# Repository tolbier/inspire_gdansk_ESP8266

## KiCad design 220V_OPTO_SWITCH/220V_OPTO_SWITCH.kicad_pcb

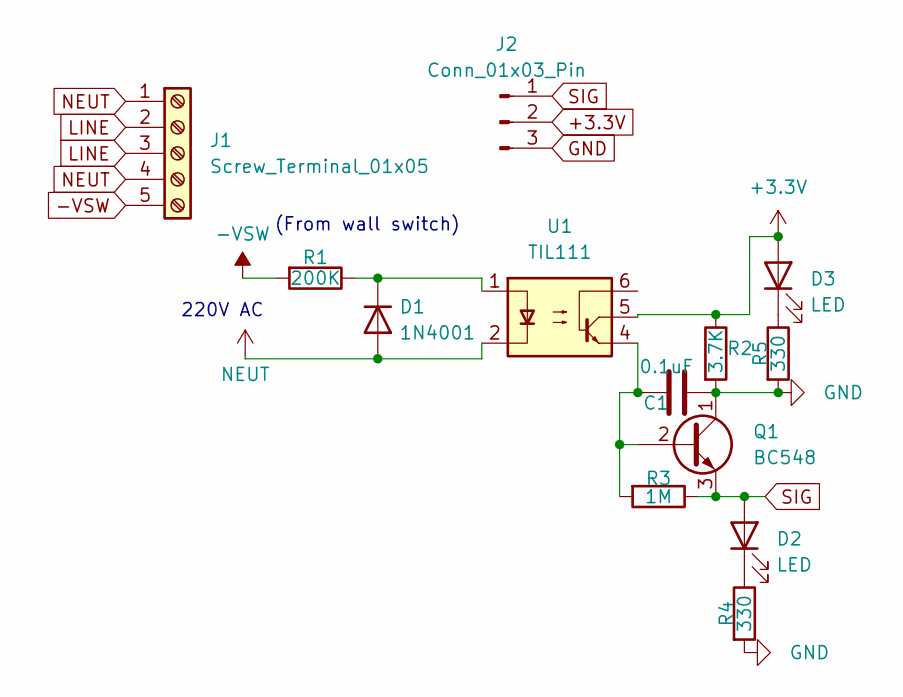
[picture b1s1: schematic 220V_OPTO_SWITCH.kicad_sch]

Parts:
C1: 0.1uF; C_1206_3216Metric_Pad1.33x1.80mm_HandSolder
D1: 1N4001; D_DO-41_SOD81_P10.16mm_Horizontal
D2, D3: LED; LED_0805_2012Metric_Pad1.15x1.40mm_HandSolder
J1: Screw_Terminal_01x05; TerminalBlock_Phoenix_MKDS-1,5-5_1x05_P5.00mm_Horizontal
J2: Conn_01x03_Pin; PinHeader_1x03_P2.54mm_Vertical
Q1: BC548; TO-92_Inline
R1: 200K; R_Axial_DIN0411_L9.9mm_D3.6mm_P15.24mm_Horizontal
R2: 3.7K; R_0805_2012Metric_Pad1.20x1.40mm_HandSolder
R3: 1M; R_0805_2012Metric_Pad1.20x1.40mm_HandSolder
R4, R5: 330; R_0805_2012Metric_Pad1.20x1.40mm_HandSolder
U1: TIL111; DIP-6_W7.62mm

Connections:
+3.3V: D3.2 (A), J2.2, R2.1, U1.5
-VSW: J1.5, R1.2
GND: C1.2, J2.3, Q1.1 (C), R2.2, R4.2, R5.2
LINE: J1.2, J1.3
NEUT: D1.2 (A), J1.1, J1.4, U1.2
unnamed: D1.1 (K), R1.1, U1.1
unnamed: D2.1 (K), R4.1
unnamed: D3.1 (K), R5.1
unnamed: C1.1, Q1.2 (B), R3.2, U1.4
SIG: D2.2 (A), J2.1, Q1.3 (E), R3.1

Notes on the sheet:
(From wall switch)
220V AC

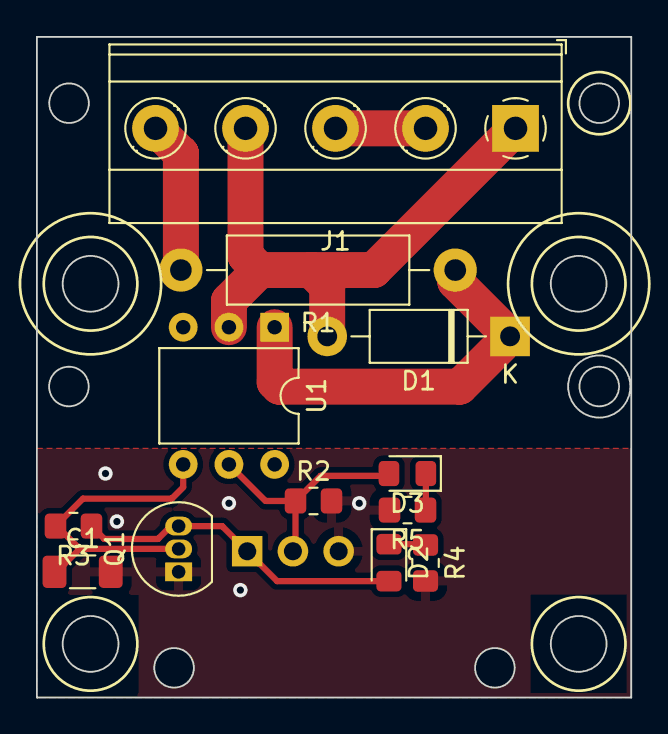
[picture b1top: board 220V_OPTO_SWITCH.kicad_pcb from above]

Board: 2 copper layers, 33.0 x 36.7 mm, 13 parts (1 on the bottom side), 10 nets.

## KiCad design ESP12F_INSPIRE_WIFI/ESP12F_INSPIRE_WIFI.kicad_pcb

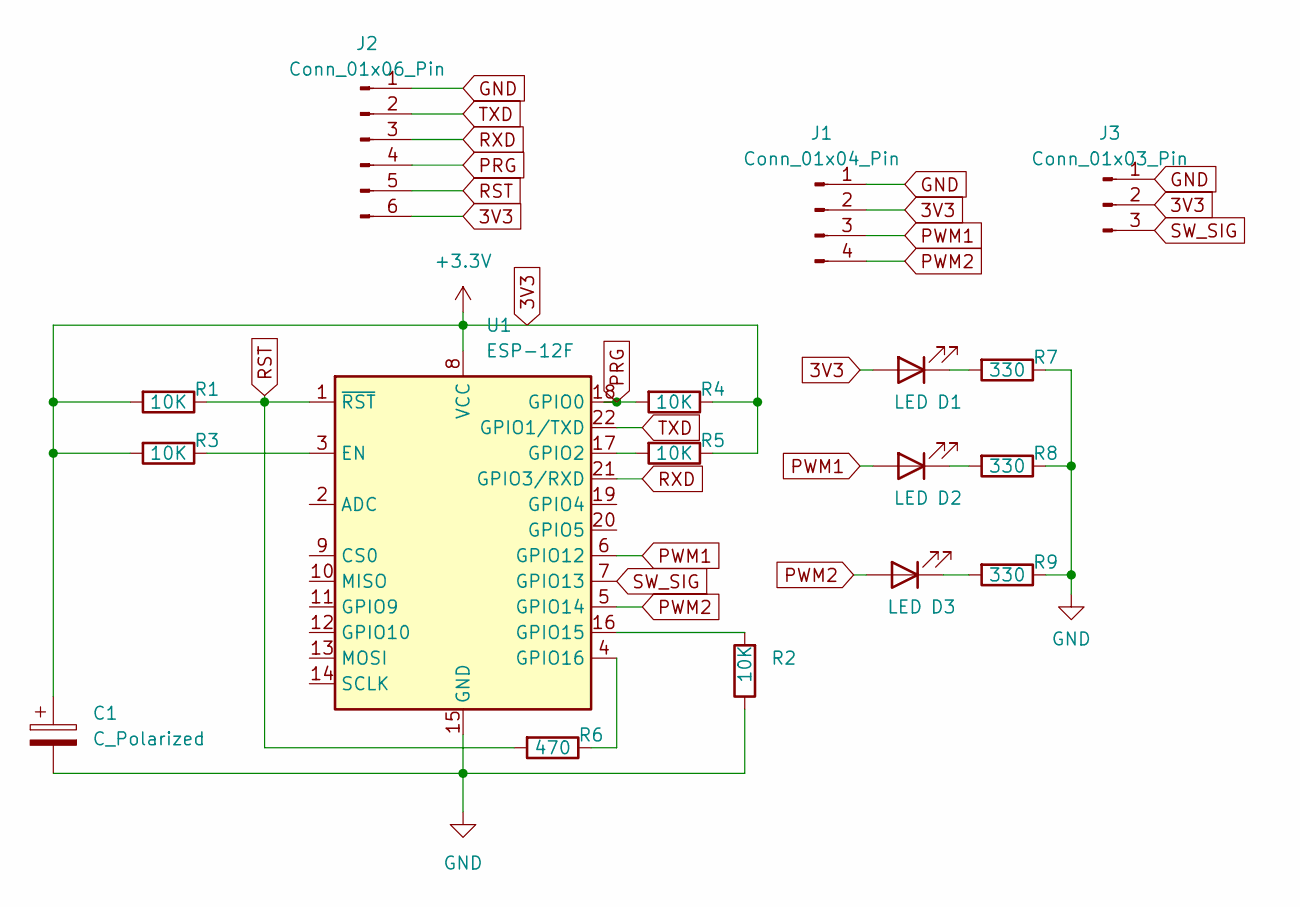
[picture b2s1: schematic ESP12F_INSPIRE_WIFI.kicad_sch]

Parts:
C1: C_Polarized; CP_Elec_3x5.4
D1, D2, D3: LED; LED_0805_2012Metric
J1: Conn_01x04_Pin; PinSocket_1x04_P2.54mm_Vertical
J2: Conn_01x06_Pin; PinHeader_1x06_P2.00mm_Vertical
J3: Conn_01x03_Pin; PinSocket_1x03_P2.54mm_Vertical
R1, R2, R3, R4, R5: 10K; R_0805_2012Metric
R6: 470; R_0805_2012Metric
R7, R8, R9: 330; R_0805_2012Metric
U1: ESP-12F; ESP-12E

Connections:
3V3: C1.1, D1.2 (A), J1.2, J2.6, J3.2, R1.2, R3.2, R4.1, R5.1, U1.8 (VCC)
GND: C1.2, J1.1, J2.1, J3.1, R2.1, R7.1, R8.1, R9.1, U1.15 (GND)
unnamed: D1.1 (K), R7.2
unnamed: D2.1 (K), R8.2
unnamed: D3.1 (K), R9.2
unnamed: R3.1, U1.3 (EN)
unnamed: R5.2, U1.17 (GPIO2)
unnamed: R2.2, U1.16 (GPIO15)
unnamed: R6.1, U1.4 (GPIO16)
PRG: J2.4, R4.2, U1.18 (GPIO0)
PWM1: D2.2 (A), J1.3, U1.6 (GPIO12)
PWM2: D3.2 (A), J1.4, U1.5 (GPIO14)
RST: J2.5, R1.1, R6.2, U1.1 (~RST)
RXD: J2.3, U1.21 (GPIO3/RXD)
SW_SIG: J3.3, U1.7 (GPIO13)
TXD: J2.2, U1.22 (GPIO1/TXD)

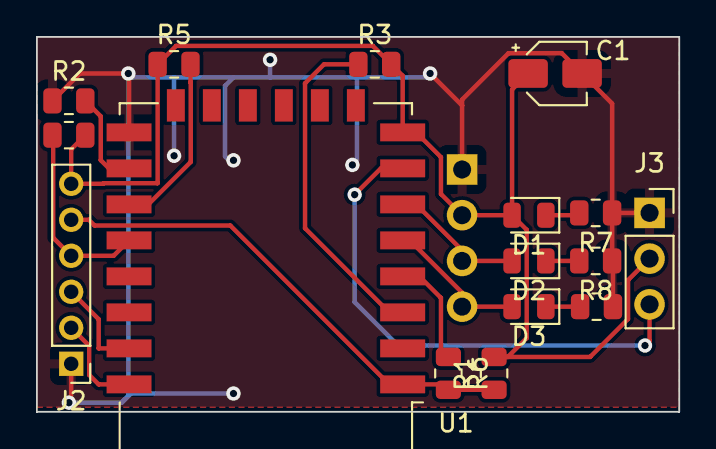
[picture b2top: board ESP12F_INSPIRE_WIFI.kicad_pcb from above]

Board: 2 copper layers, 35.7 x 20.8 mm, 17 parts (1 on the bottom side), 16 nets.

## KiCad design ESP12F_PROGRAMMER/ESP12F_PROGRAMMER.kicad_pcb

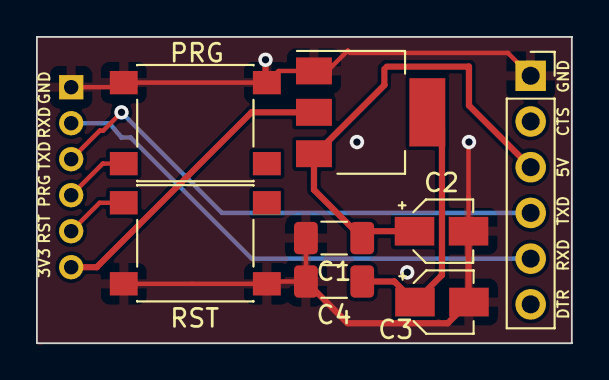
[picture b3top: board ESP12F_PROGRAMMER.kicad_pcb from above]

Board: 2 copper layers, 29.7 x 17.0 mm, 9 parts (1 on the bottom side), 7 nets.

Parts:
C1, C4: 100nf; C_1206_3216Metric_Pad1.33x1.80mm_HandSolder
C2, C3: 10uF; CP_Elec_3x5.3
J1: Conn_01x06_Pin; PinHeader_1x06_P2.00mm_Vertical
J2: Conn_01x06_Pin; PinSocket_1x06_P2.54mm_Vertical
PRG: SW_Push; SW_Push_1P1T_NO_6x6mm_H9.5mm
RST: SW_Push; SW_Push_1P1T_NO_6x6mm_H9.5mm
U1: AMS1117-3.3; SOT-223-3_TabPin2

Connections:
3V3: C3.1, C4.1, J1.6, U1.2 (VO)
5V: C1.1, C2.1, J2.3, U1.3 (VI)
GND: C1.2, C2.2, C3.2, C4.2, J1.1, J2.1, PRG.2, RST.2, U1.1 (GND)
PRG: J1.4, PRG.1
RST: J1.5, RST.1
RXD: J1.2, J2.5
TXD: J1.3, J2.4
